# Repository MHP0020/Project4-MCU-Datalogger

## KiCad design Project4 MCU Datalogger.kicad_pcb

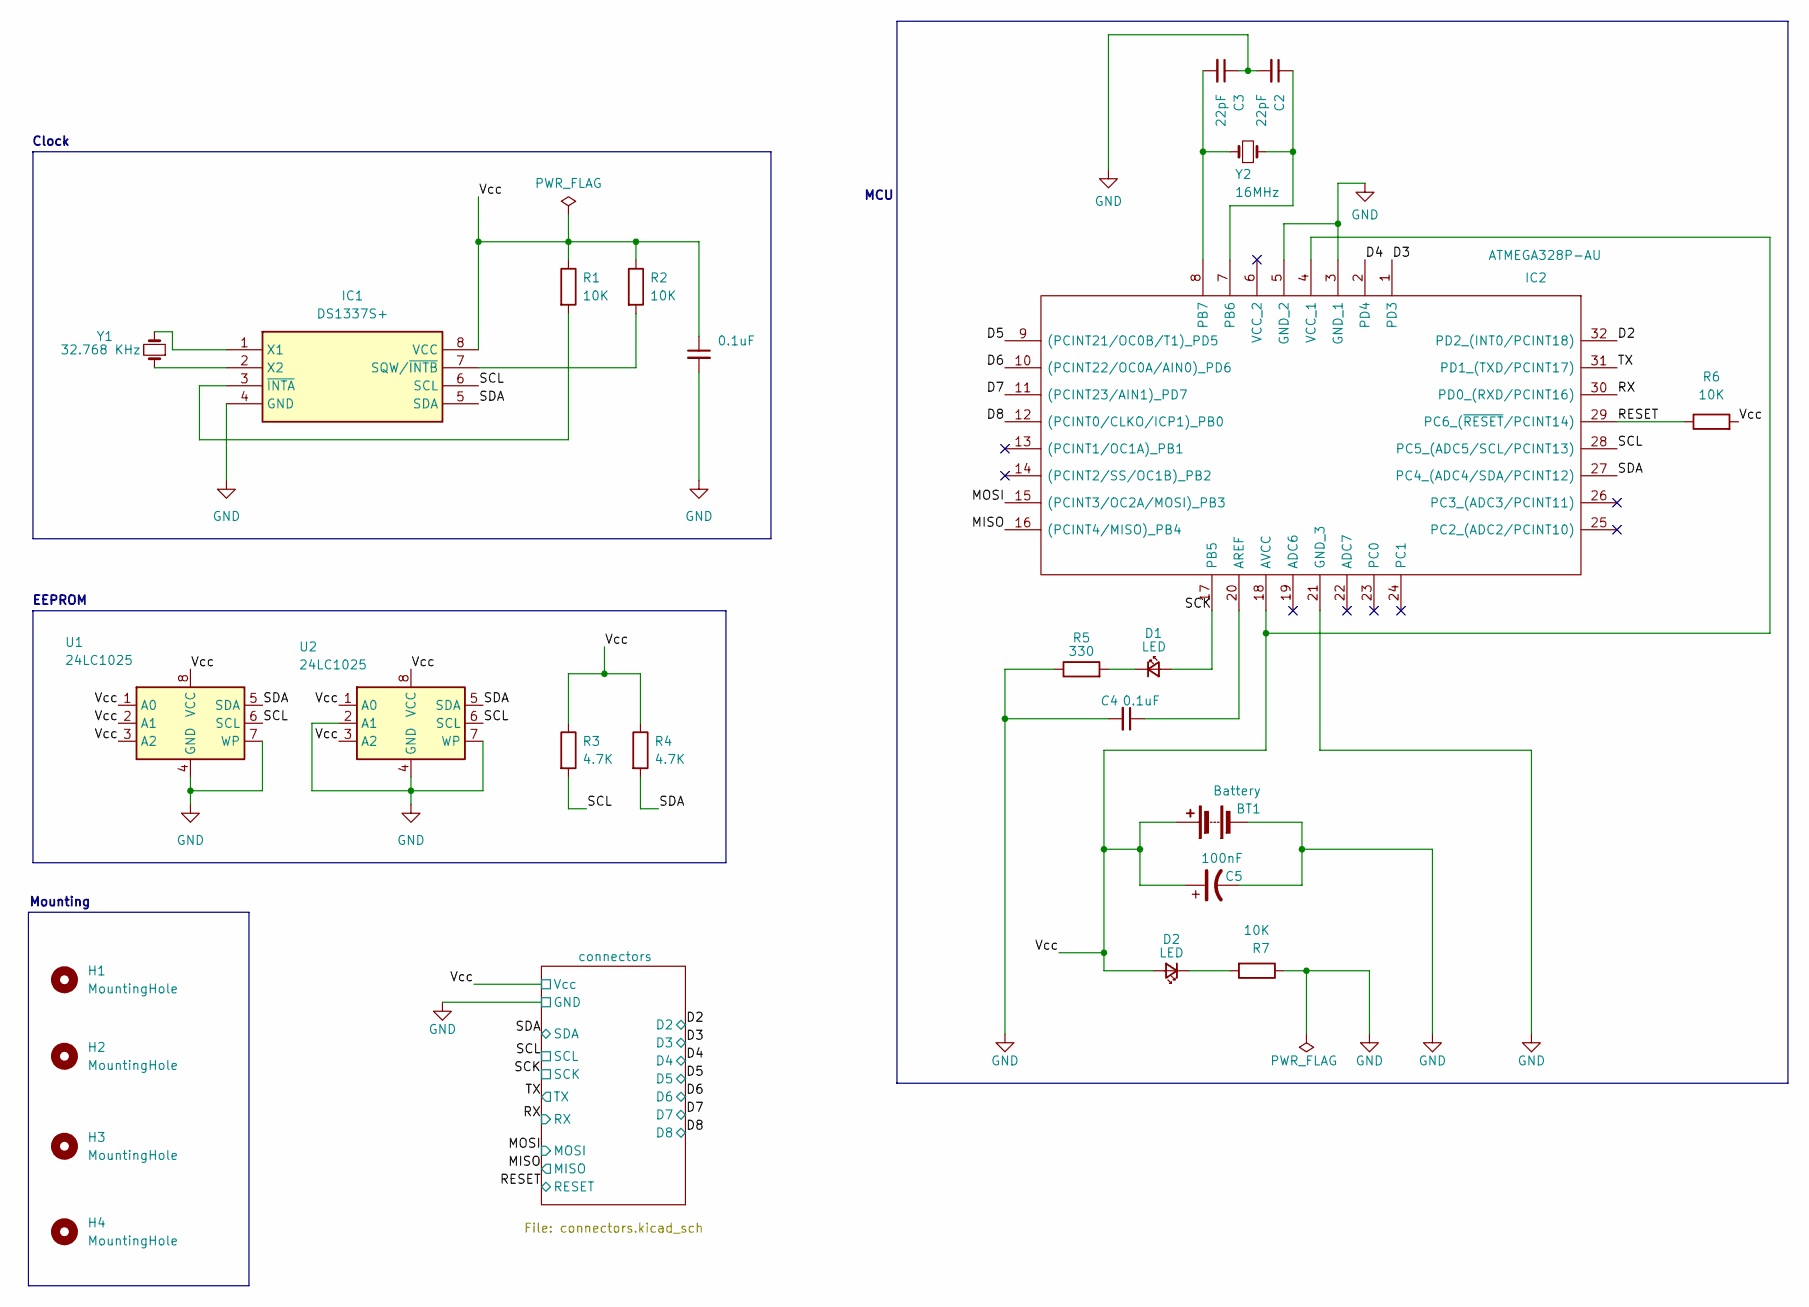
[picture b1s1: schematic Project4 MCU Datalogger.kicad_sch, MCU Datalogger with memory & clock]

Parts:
BT1: Battery; PinHeader_1x02_P2.54mm_Vertical
C1, C4: 0.1uF; C_0805_2012Metric; Voltage 1kV; Tolerance 100%
C2, C3: 22pF; C_0805_2012Metric; Voltage 1kV; Tolerance 100%
C5: 100nF; C_0805_2012Metric; Voltage 1kV; Tolerance 100%
D1, D2: LED; LED_0805_2012Metric
H1, H2, H3, H4: MountingHole; MountingHole_2.1mm
IC1: DS1337S+; SOIC127P600X175-8N; Manufacturer_Part_Number DS1337S+
IC2: ATMEGA328P-AU; QFP80P900X900X120-32N; Manufacturer_Part_Number ATMEGA328P-AU
R1, R2, R6, R7: 10K; R_0805_2012Metric
R3, R4: 4.7K; R_0805_2012Metric
R5: 330; R_0805_2012Metric
U1, U2: 24LC1025; SOIC-8_3.9x4.9mm_P1.27mm
Y1: 32.768 KHz; Crystal_SMD_5032-2Pin_5.0x3.2mm_HandSoldering
Y2: 16MHz; Crystal_SMD_5032-2Pin_5.0x3.2mm_HandSoldering

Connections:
/D2: IC2.32 (PD2_(INT0/PCINT18)); also elsewhere on the board
/D3: IC2.1 (PD3); also elsewhere on the board
/D4: IC2.2 (PD4); also elsewhere on the board
/D5: IC2.9 ((PCINT21/OC0B/T1)_PD5); also elsewhere on the board
/D6: IC2.10 ((PCINT22/OC0A/AIN0)_PD6); also elsewhere on the board
/D7: IC2.11 ((PCINT23/AIN1)_PD7); also elsewhere on the board
/D8: IC2.12 ((PCINT0/CLKO/ICP1)_PB0); also elsewhere on the board
/MISO: IC2.16 ((PCINT4/MISO)_PB4); also elsewhere on the board
/MOSI: IC2.15 ((PCINT3/OC2A/MOSI)_PB3); also elsewhere on the board
/RESET: IC2.29 (PC6_(~RESET/PCINT14)), R6.1; also elsewhere on the board
/RX: IC2.30 (PD0_(RXD/PCINT16)); also elsewhere on the board
/SCK: D1.2 (A), IC2.17 (PB5); also elsewhere on the board
/SCL: IC1.6 (SCL), IC2.28 (PC5_(ADC5/SCL/PCINT13)), R3.2, U1.6 (SCL), U2.6 (SCL); also elsewhere on the board
/SDA: IC1.5 (SDA), IC2.27 (PC4_(ADC4/SDA/PCINT12)), R4.2, U1.5 (SDA), U2.5 (SDA); also elsewhere on the board
/TX: IC2.31 (PD1_(TXD/PCINT17)); also elsewhere on the board
/Vcc: BT1.1 (+), C1.1, C5.1, D2.2 (A), IC1.8 (VCC), IC2.4 (VCC_1), IC2.18 (AVCC), R1.1, R2.1, R3.1, R4.1, R6.2, U1.1 (A0), U1.2 (A1), U1.3 (A2), U1.8 (VCC), U2.1 (A0), U2.3 (A2), U2.8 (VCC); also elsewhere on the board
GND: BT1.2 (-), C1.2, C2.2, C3.1, C4.2, C5.2, IC1.4 (GND), IC2.3 (GND_1), IC2.5 (GND_2), IC2.21 (GND_3), R5.1, R7.1, U1.4 (GND), U1.7 (WP), U2.2 (A1), U2.4 (GND), U2.7 (WP); also elsewhere on the board
unnamed: D1.1 (K), R5.2
unnamed: D2.1 (K), R7.2
unnamed: IC1.7 (SQW/~INTB), R2.2
unnamed: IC1.1 (X1), Y1.2
unnamed: IC1.2 (X2), Y1.1
unnamed: IC1.3 (~INTA), R1.2
unnamed: C4.1, IC2.20 (AREF)
unnamed: C2.1, IC2.7 (PB6), Y2.2
unnamed: C3.2, IC2.8 (PB7), Y2.1

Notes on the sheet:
Mounting
Clock
MCU
EEPROM

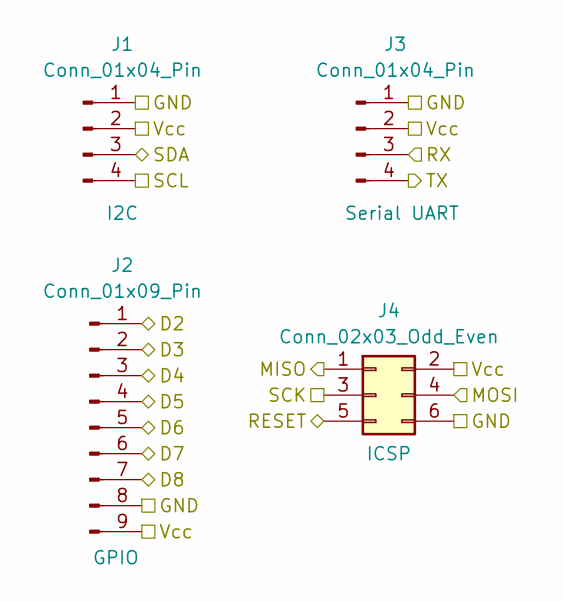
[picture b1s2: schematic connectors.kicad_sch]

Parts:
J1, J3: Conn_01x04_Pin; PinHeader_1x04_P2.54mm_Vertical
J2: Conn_01x09_Pin; PinHeader_1x09_P2.54mm_Vertical
J4: Conn_02x03_Odd_Even; PinHeader_2x03_P2.54mm_Vertical

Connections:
/D2: J2.1; also elsewhere on the board
/D3: J2.2; also elsewhere on the board
/D4: J2.3; also elsewhere on the board
/D5: J2.4; also elsewhere on the board
/D6: J2.5; also elsewhere on the board
/D7: J2.6; also elsewhere on the board
/D8: J2.7; also elsewhere on the board
/MISO: J4.1; also elsewhere on the board
/MOSI: J4.4; also elsewhere on the board
/RESET: J4.5; also elsewhere on the board
/RX: J3.3; also elsewhere on the board
/SCK: J4.3; also elsewhere on the board
/SCL: J1.4; also elsewhere on the board
/SDA: J1.3; also elsewhere on the board
/TX: J3.4; also elsewhere on the board
/Vcc: J1.2, J2.9, J3.2, J4.2; also elsewhere on the board
GND: J1.1, J2.8, J3.1, J4.6; also elsewhere on the board

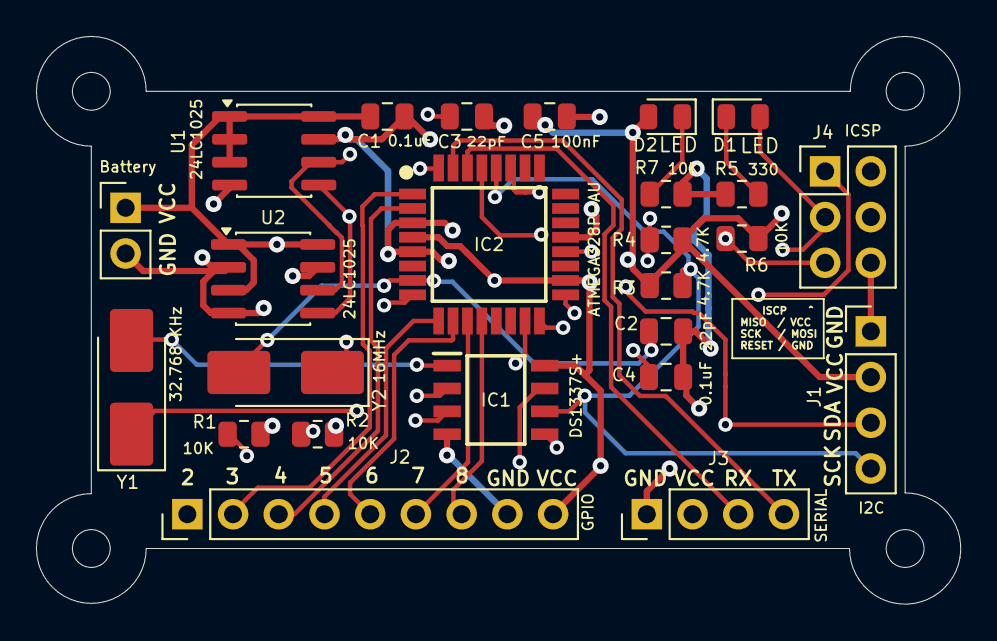
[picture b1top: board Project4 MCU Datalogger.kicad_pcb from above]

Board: 4 copper layers, 51.3 x 31.5 mm, 29 parts (0 on the bottom side), 26 nets.
